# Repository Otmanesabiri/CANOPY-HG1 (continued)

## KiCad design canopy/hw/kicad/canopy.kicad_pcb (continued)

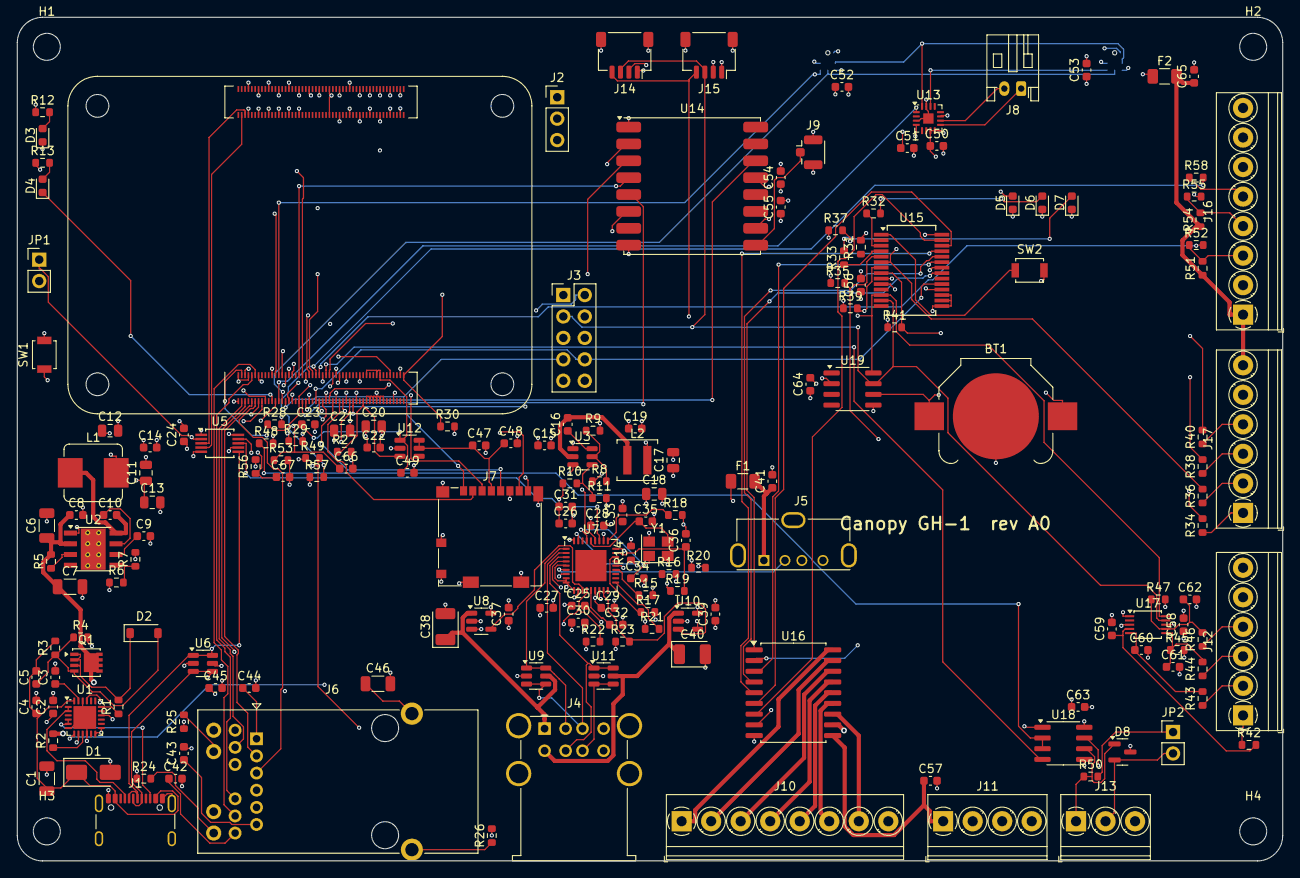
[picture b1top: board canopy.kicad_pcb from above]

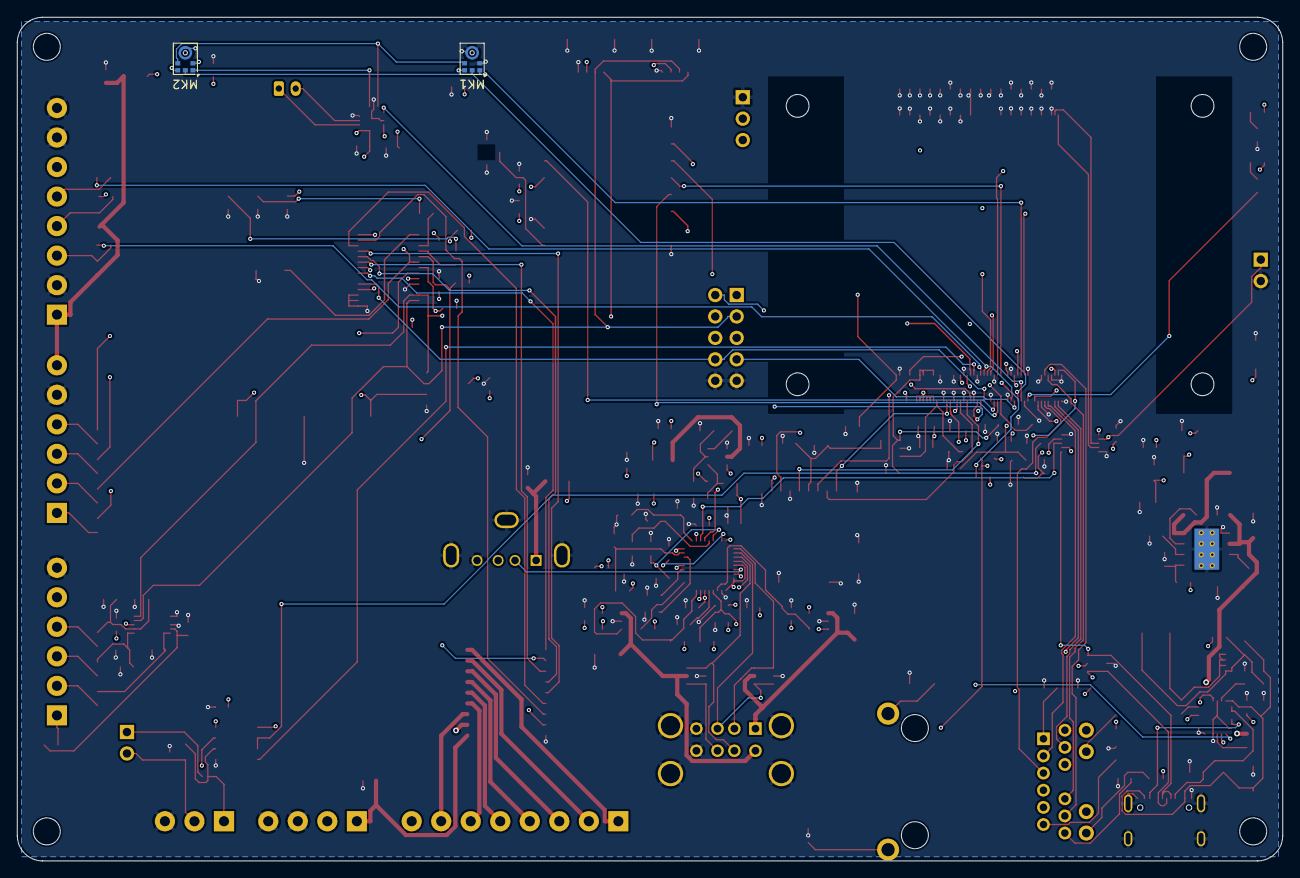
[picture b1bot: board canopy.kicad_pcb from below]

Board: 4 copper layers, 150.0 x 100.0 mm, 186 parts (2 on the bottom side), 162 nets.

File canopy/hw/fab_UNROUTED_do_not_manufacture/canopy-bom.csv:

Qty,References,Value,Description,Manufacturer,MPN,Footprint
1,J1,USB-C PD IN,"USB Type-C receptacle, USB2.0, 16-pin",GCT,USB4105-GF-A,USB_C_Receptacle_GCT_USB4105-xx-A_16P_TopMnt_Horizontal
1,D1,SMAJ22A,TVS 22V 400W,Littelfuse,SMAJ22A,D_SMA
3,C1 C6 C7,10u/35V,10uF 35V X5R 1206,Murata,GRM31CR6YA106KA12L,C_1206_3216Metric
1,U1,STUSB4500,Standalone USB PD sink controller,STMicroelectronics,STUSB4500QTR,QFN-24-1EP_4x4mm_P0.5mm_EP2.7x2.7mm
13,R1 R2 R12 R13 R31 R32 R33 R34 R36 R38 R40 R42 R43,1k,Resistor 1% 0603,Yageo,RC0603FR-071KL,R_0603_1608Metric
7,C2 C3 C4 C9 C32 C36 C49,1u,1uF 50V X5R 0603,Samsung,CL10A105KB8NNNC,C_0603_1608Metric
1,Q1,SiS443DN,P-MOSFET -40V PowerPAK 1212-8 (PD load switch),Vishay,SIS443DN-T1-GE3,Vishay_PowerPAK_1212-8_Single
8,R3 R5 R6 R9 R10 R27 R28 R29,100k,Resistor 1% 0603,Yageo,RC0603FR-07100KL,R_0603_1608Metric
3,R4 R52 R55,22k,Resistor 1% 0603,Yageo,RC0603FR-0722KL,R_0603_1608Metric
34,C5 C8 C10 C14 C16 C19 C22 C23 C24 C25 C26 C27 C28 C29 C30 C33 C42 C43 C44 C45 C48 C51 C52 C53 C55 C56 C57 C58 C59 C60 C61 C62 C63 C64,100n,100nF 50V X7R 0603,Murata,GRM188R71H104KA93D,C_0603_1608Metric
1,D2,BZT52C10,Zener 10V gate clamp,Diodes Inc.,BZT52C10-7-F,D_SOD-123
1,U2,LMR33640A,"36V 4A synchronous buck, 400kHz",Texas Instruments,LMR33640ADDAR,Texas_HSOP-8-1EP_3.9x4.9mm_P1.27mm_ThermalVias
1,R7,24.9k,Resistor 1% 0603,Yageo,RC0603FR-0724K9L,R_0603_1608Metric
1,L1,6.8uH,Shielded power inductor 6.8uH,Bourns,SRP7028A-6R8M,L_Bourns_SRP7028A_7.3x6.6mm
7,C11 C12 C13 C17 C18 C20 C21,22u,22uF 10V X5R 0805,Murata,GRM21BR61A226ME44L,C_0805_2012Metric
1,U3,AP62250,18V 2.5A synchronous buck,Diodes Inc.,AP62250WU-7,TSOT-23-6
19,R8 R15 R16 R17 R18 R19 R20 R21 R22 R23 R30 R35 R37 R39 R41 R45 R47 R48 R49,10k,Resistor 1% 0603,Yageo,RC0603FR-0710KL,R_0603_1608Metric
1,R11,31.6k,Resistor 1% 0603,Yageo,RC0603FR-0731K6L,R_0603_1608Metric
9,C15 C31 C37 C39 C41 C47 C50 C54 C65,10u,10uF 10V X5R 0603,Murata,GRM188R61A106KE69D,C_0603_1608Metric
1,L2,2.2uH,Shielded power inductor 2.2uH,Coilcraft,XAL4020-222MEC,L_Coilcraft_XAL4020-XXX
2,D3 D6,green,LED green 0603,Lite-On,LTST-C191KGKT,LED_0603_1608Metric
1,U4,Raspberry Pi CM4,Compute Module 4 (BCM2711) on 2x Hirose DF40C-100DS-0.4V(51),Raspberry Pi,"CM4102000 (2GB, Wi-Fi/BT, Lite) or CM4102032 (32GB eMMC)",Raspberry-Pi-4-Compute-Module
1,JP1,USB BOOT,Fit jumper to flash eMMC over USB-C (rpiboot),Harwin,M20-9990245,PinHeader_1x02_P2.54mm_Vertical
1,SW1,RESET,Tact switch,Omron,B3U-1000P,SW_SPST_B3U-1000P
1,D4,yellow,LED yellow 0603,Lite-On,LTST-C191KSKT,LED_0603_1608Metric
1,J2,DEBUG UART,3.3V serial console,Harwin,M20-9990345,PinHeader_1x03_P2.54mm_Vertical
1,J3,EXPANSION,"Expansion header (I2C, 2x PWM, GPIO)",Harwin,M20-9980545,PinHeader_2x05_P2.54mm_Vertical
1,U5,FSUSB42,"USB2.0 HS 2:1 switch: SEL=0 -> USB-C (rpiboot), SEL=1 -> hub",onsemi,FSUSB42MUX,MSOP-10_3x3mm_P0.5mm
3,U6 U9 U11,USBLC6-2,USB ESD protection,STMicroelectronics,USBLC6-2SC6,SOT-23-6
1,U7,USB2514B,USB 2.0 HS 4-port hub (port 4 strapped off),Microchip,USB2514B-I/M2,QFN-36-1EP_6x6mm_P0.5mm_EP3.7x3.7mm
1,R14,12k,Resistor 1% 0603,Yageo,RC0603FR-0712KL,R_0603_1608Metric
1,Y1,24MHz,Crystal 24MHz 18pF 3225,Abracon,ABM8-24.000MHZ-B2-T,Crystal_SMD_3225-4Pin_3.2x2.5mm
2,C34 C35,18p,18pF 50V C0G 0603,Murata,GRM1885C1H180JA01D,C_0603_1608Metric
2,U8 U10,TPS2065C,"USB port power switch 1A, active-high EN",Texas Instruments,TPS2065CDBVR,SOT-23-5
2,C38 C40,150u,150uF 6.3V polymer,KEMET,T520B157M006ATE070,CP_EIA-3528-21_Kemet-B
1,J4,USB-A x2,Dual stacked USB-A,Wurth Elektronik,61400826021,USB_A_Wuerth_61400826021_Horizontal_Stacked
1,F1,0.75A,PTC 0.75A hold,Littelfuse,1206L075THYR,Fuse_1206_3216Metric
1,J5,USB-A internal (Zigbee),"Vertical USB-A, internal port for Zigbee/Thread coordinator stick",Molex,105057-0001,USB_A_Molex_105057_Vertical
1,J6,RJ45 GbE,RJ45 with 1000BASE-T magnetics and LEDs,Pulse Electronics,JK0654219NL,RJ45_Pulse_JK0654219NL_Horizontal
2,R24 R25,330R,Resistor 1% 0603,Yageo,RC0603FR-07330RL,R_0603_1608Metric
1,C46,1n/2kV,1nF 2kV X7R 1206,KEMET,C1206C102KGRACTU,C_1206_3216Metric
1,R26,1M,Resistor 1% 0603,Yageo,RC0603FR-071ML,R_0603_1608Metric
1,J7,microSD,microSD push-pull socket,Molex,104031-0811,microSD_HC_Molex_104031-0811
1,U12,TPS22917,SD card power switch (lets CM4 power-cycle the card),Texas Instruments,TPS22917DBVR,SOT-23-6
1,U13,MAX98357A,I2S 3W class-D mono amplifier,Analog Devices,MAX98357AETE+T,TQFN-16-1EP_3x3mm_P0.5mm_EP1.23x1.23mm
1,J8,SPEAKER 4-8R,Speaker connector,JST,S2B-PH-K-S(LF)(SN),JST_PH_S2B-PH-K_1x02_P2.00mm_Horizontal
2,MK1 MK2,ICS-43434,"I2S MEMS microphone, bottom port (left channel)",TDK InvenSense,ICS-43434,InvenSense_ICS-43434-6_3.5x2.65mm
1,U14,RFM95W,"LoRa transceiver module SX1276, 915MHz (868MHz: RFM95W-868S2)",HopeRF,RFM95W-915S2,HOPERF_RFM9XW_SMD
1,J9,LoRa ANT,U.FL antenna connector,Hirose,U.FL-R-SMT-1(10),U.FL_Hirose_U.FL-R-SMT-1_Vertical
1,U15,MCP23017,I2C 16-bit I/O expander @0x20; held in reset by CM4 nEXTRST,Microchip,MCP23017-E/SS,SSOP-28_5.3x10.2mm_P0.65mm
1,U16,ULN2803A,8x Darlington sink driver 50V/500mA with clamp diodes,Texas Instruments,ULN2803ADWR,SOIC-18W_7.5x11.6mm_P1.27mm
1,J10,OUT1-8 (sink),Screw terminal 8-pos 3.5mm,Phoenix Contact,"PT 1,5/8-3,5-H (1984675)","TerminalBlock_Phoenix_PT-1,5-8-3.5-H_1x08_P3.50mm_Horizontal"
1,J11,V_FIELD / GND,Screw terminal 4-pos 3.5mm,Phoenix Contact,"PT 1,5/4-3,5-H (1984633)","TerminalBlock_Phoenix_PT-1,5-4-3.5-H_1x04_P3.50mm_Horizontal"
1,SW2,USER / TALK,Tact switch,Omron,B3U-1000P,SW_SPST_B3U-1000P
1,D5,red,LED red 0603,Lite-On,LTST-C191KRKT,LED_0603_1608Metric
1,D7,blue,LED blue 0603,Lite-On,LTST-C191TBKT,LED_0603_1608Metric
1,U17,ADS1115,16-bit 4-ch I2C ADC @0x48,Texas Instruments,ADS1115IDGSR,TSSOP-10_3x3mm_P0.5mm
2,R44 R46,20k,Resistor 1% 0603,Yageo,RC0603FR-0720KL,R_0603_1608Metric
1,J12,AIN0-1 3V3 / AIN2-3 10V,Screw terminal 6-pos 3.5mm,Phoenix Contact,"PT 1,5/6-3,5-H (1984659)","TerminalBlock_Phoenix_PT-1,5-6-3.5-H_1x06_P3.50mm_Horizontal"
1,U18,THVD1420,3.3V half-duplex RS-485 transceiver,Texas Instruments,THVD1420DR,SOIC-8_3.9x4.9mm_P1.27mm
1,D8,SM712,RS-485 TVS,Semtech,SM712.TCT,SOT-23
1,R50,120R,Resistor 1% 0603,Yageo,RC0603FR-07120RL,R_0603_1608Metric
1,JP2,RS485 TERM,Fit jumper for 120R bus termination,Harwin,M20-9990245,PinHeader_1x02_P2.54mm_Vertical
1,J13,RS485 A/B/GND,Screw terminal 3-pos 3.5mm,Phoenix Contact,"PT 1,5/3-3,5-H (1984620)","TerminalBlock_Phoenix_PT-1,5-3-3.5-H_1x03_P3.50mm_Horizontal"
1,U19,DS3231M,I2C RTC +/-5ppm @0x68,Analog Devices,DS3231MZ+TRL,SOIC-8_3.9x4.9mm_P1.27mm
1,BT1,CR1220,CR1220 coin cell holder,Keystone,3000,BatteryHolder_Keystone_3000_1x12mm
2,J14 J15,I2C (Qwiic),Qwiic / STEMMA QT I2C sensor port,JST,SM04B-SRSS-TB(LF)(SN),JST_SH_SM04B-SRSS-TB_1x04-1MP_P1.00mm_Horizontal
1,F2,0.5A,PTC 0.5A hold,Bel Fuse,0ZCJ0050FF2G,Fuse_1206_3216Metric
3,R51 R54 R57,4.7k,Resistor 1% 0603,Yageo,RC0603FR-074K7L,R_0603_1608Metric
2,R53 R56,33k,Resistor 1% 0603,Yageo,RC0603FR-0733KL,R_0603_1608Metric
2,C66 C67,1n,1nF 50V X7R 0603,Murata,GRM188R71H102KA01D,C_0603_1608Metric
1,R58,100R,Resistor 1% 0603,Yageo,RC0603FR-07100RL,R_0603_1608Metric
1,J16,5V/FLOW1/FLOW2/1W/3V3,Screw terminal 8-pos 3.5mm,Phoenix Contact,"PT 1,5/8-3,5-H (1984675)","TerminalBlock_Phoenix_PT-1,5-8-3.5-H_1x08_P3.50mm_Horizontal"
1,J17,DI1-4 (dry contact),Screw terminal 6-pos 3.5mm,Phoenix Contact,"PT 1,5/6-3,5-H (1984659)","TerminalBlock_Phoenix_PT-1,5-6-3.5-H_1x06_P3.50mm_Horizontal"
2,(U4 sockets),100-pin 0.4mm,CM4 mating connector - part of the U4 footprint,Hirose,DF40C-100DS-0.4V(51),
4,(U4 standoffs),M2.5 x 1.5 mm,SMT/press-fit spacer for CM4 (3.0 mm stack height uses DF40HC(3.0)),Wurth Elektronik,9774015151R,
1,(BT1 cell),CR1220,3V lithium coin cell,Panasonic,CR1220,

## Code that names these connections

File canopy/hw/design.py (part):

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S = 'cm4'
cm4 = {int(k): v for k, v in json.load(open(os.path.join(HERE, 'cm4_pins.json'))).items()}
GP = {2: 'I2C_SDA', 3: 'I2C_SCL', 4: 'RS485_TX', 5: 'RS485_RX', 6: 'RS485_DE', 7: 'AMP_SD', 8: 'LORA_NSS',
      9: 'SPI_MISO', 10: 'SPI_MOSI', 11: 'SPI_SCK', 12: 'GPIO12_PWM0', 13: 'GPIO13_PWM1', 14: 'UART_TX',
      15: 'UART_RX', 16: 'GPIO16', 17: 'FLOW1', 18: 'I2S_BCLK', 19: 'I2S_LRCLK', 20: 'I2S_DIN', 21: 'I2S_DOUT',
      22: 'LORA_RST', 23: 'IOX_INT', 24: 'LORA_DIO1', 25: 'LORA_DIO0', 26: 'FLOW2', 27: 'ONEWIRE'}
cm_nets = {}
for n, name in cm4.items():
    if name == 'GND': cm_nets[str(n)] = 'GND'
    elif name == '+5V': cm_nets[str(n)] = '+5V'
    elif name.startswith('CM4_3.3V'): cm_nets[str(n)] = 'CM4_3V3'
    elif name == 'GPIO_VREF': cm_nets[str(n)] = 'CM4_3V3'
    elif name.startswith('GPIO') and name[4:].isdigit() and int(name[4:]) in GP: cm_nets[str(n)] = GP[int(name[4:])]
    elif name.startswith('Ethernet_Pair'): cm_nets[str(n)] = 'ETH' + name[13] + '_' + name[-1]
    elif name.startswith('SD_DAT') and name[-1] in '0123': cm_nets[str(n)] = name
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P('J', S, 'Connector_Generic:Conn_01x03', 'DEBUG UART', 'Connector_PinHeader_2.54mm:PinHeader_1x03_P2.54mm_Vertical',
  {'1': 'GND', '2': 'UART_TX', '3': 'UART_RX'}, 'M20-9990345', 'Harwin', '3.3V serial console')     # J2
P('J', S, 'Connector_Generic:Conn_02x05_Odd_Even', 'EXPANSION', 'Connector_PinHeader_2.54mm:PinHeader_2x05_P2.54mm_Vertical',
  {'1': '+3V3', '2': '+5V', '3': 'I2C_SDA', '4': 'I2C_SCL', '5': 'GPIO12_PWM0', '6': 'GPIO13_PWM1', '7': 'GPIO16',
   '8': 'IOX_INT', '9': 'GND', '10': 'GND'}, 'M20-9980545', 'Harwin', 'Expansion header (I2C, 2x PWM, GPIO)')  # J3
for i in range(4):
    P('H', S, 'Mechanical:MountingHole', 'M3', 'MountingHole:MountingHole_3.2mm_M3', {}, '', '', 'Board mounting hole', dnp=True)

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  'USB2514B-I/M2', 'Microchip', 'USB 2.0 HS 4-port hub (port 4 strapped off)')                      # U7
for n in range(6): C(S, '100n', '+3V3')
C(S, '10u', '+3V3'); C(S, '1u', 'HUB_CRFILT'); C(S, '100n', 'HUB_PLLFILT'); R(S, '12k', 'HUB_RBIAS', 'GND')
P('Y', S, 'Device:Crystal_GND24', '24MHz', 'Crystal:Crystal_SMD_3225-4Pin_3.2x2.5mm', {'1': 'HUB_XI', '3': 'HUB_XO', '2': 'GND', '4': 'GND'},
  'ABM8-24.000MHZ-B2-T', 'Abracon', 'Crystal 24MHz 18pF 3225')
C(S, '18p', 'HUB_XI'); C(S, '18p', 'HUB_XO')
for n in ('HUB_NONREM1', 'HUB_CFG0', 'HUB_CFG1', 'HUB_NONREM0'): R(S, '10k', n, 'GND')
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
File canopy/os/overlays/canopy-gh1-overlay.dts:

// Canopy GH-1 carrier board overlay for Raspberry Pi CM4 (BCM2711)
//  - I2S sound card: MAX98357A amplifier (SD_MODE on GPIO7) + 2x ICS-43434 microphones, using the in-tree
//    Google voiceHAT machine driver (same codec pair), with the shutdown pin moved from GPIO16 to GPIO7
//  - UART3 (GPIO4/5) in RS-485 mode with driver-enable on GPIO6
// Everything else on the board uses stock overlays, see config.txt.
/dts-v1/;
/plugin/;

/ {
	compatible = "brcm,bcm2711";

	fragment@0 {
		target = <&i2s_clk_producer>;
		__overlay__ {
			status = "okay";
		};
	};

	fragment@1 {
		target = <&gpio>;
		__overlay__ {
			canopy_amp_pins: canopy_amp_pins {
				brcm,pins = <7>;
				brcm,function = <1>;	/* output */
				brcm,pull = <1>;	/* pull-down: amplifier muted until the driver enables it */
			};
			canopy_rs485_pins: canopy_rs485_pins {
				brcm,pins = <6>;
				brcm,function = <1>;
				brcm,pull = <1>;
			};
		};
	};

	fragment@2 {
		target-path = "/";
		__overlay__ {
			voicehat-codec {
				#sound-dai-cells = <0>;
				compatible = "google,voicehat";
				pinctrl-names = "default";
				pinctrl-0 = <&canopy_amp_pins>;
				sdmode-gpios = <&gpio 7 0>;
				status = "okay";
			};
		};
	};

	fragment@3 {
		target = <&sound>;
		__overlay__ {
			compatible = "googlevoicehat,googlevoicehat-soundcard";
			i2s-controller = <&i2s_clk_producer>;
			status = "okay";
		};
	};

	fragment@4 {
		target = <&uart3>;
		__overlay__ {
			pinctrl-names = "default";
			pinctrl-0 = <&uart3_pins &canopy_rs485_pins>;
			rts-gpios = <&gpio 6 0>;
			linux,rs485-enabled-at-boot-time;
			rs485-rts-delay = <0 0>;
			status = "okay";
		};
	};
};
